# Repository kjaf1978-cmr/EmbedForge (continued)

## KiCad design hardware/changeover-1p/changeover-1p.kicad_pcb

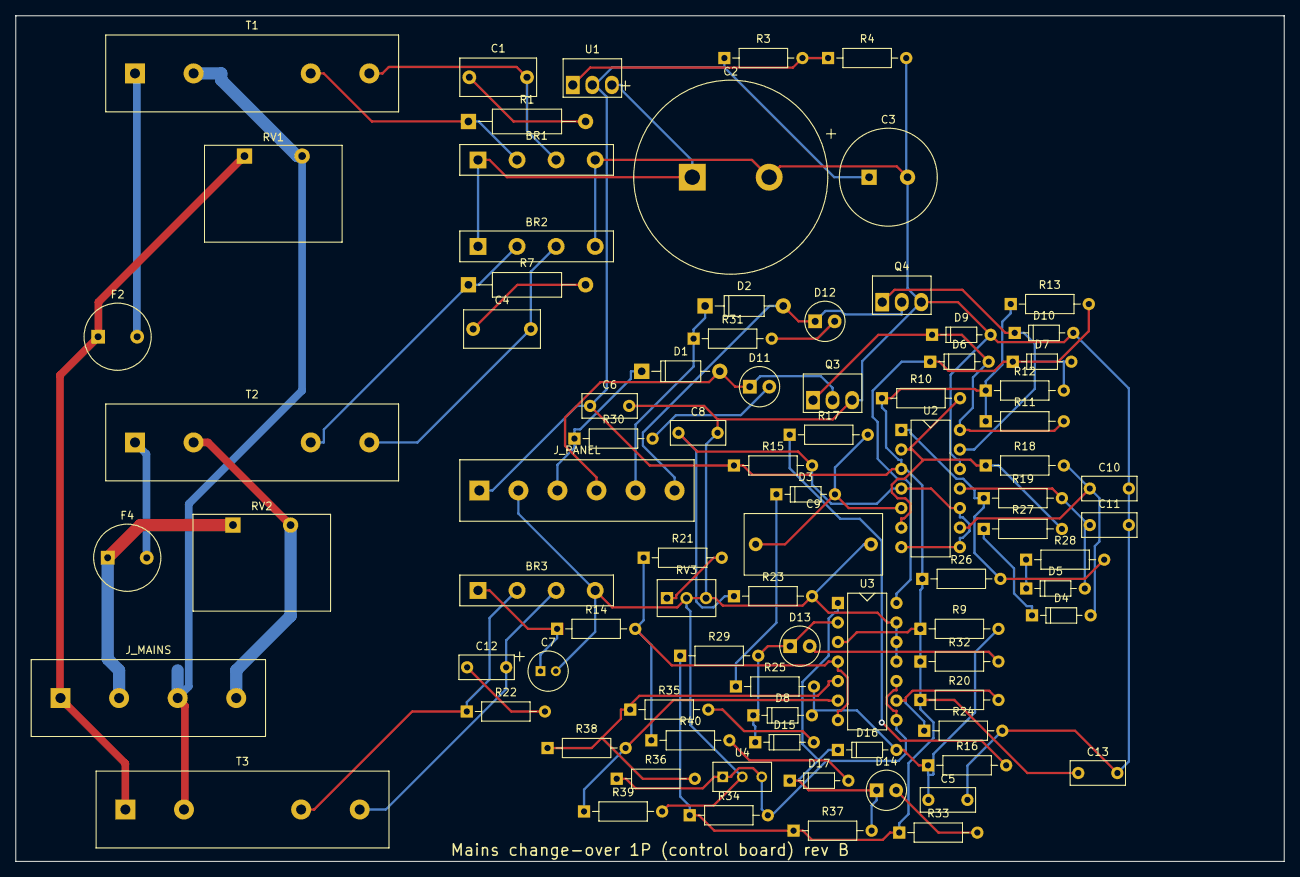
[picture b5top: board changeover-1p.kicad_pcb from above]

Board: 2 copper layers, 165.0 x 110.0 mm, 85 parts (0 on the bottom side), 52 nets.

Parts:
BR1, BR2, BR3: DB107; Bridge_Inline_4
C1, C4: 1u; C_Film_P7.5
C2: 2200u; CP_SnapIn_D25
C3: 100u; CP_Radial_D12.5
C5: 1u; C_Disc_5.08
C6, C8, C12, C13: 100n; C_Disc_5.08
C7: 4.7u; CP_Radial_D5
C9: 10u; C_Film_P15
C10, C11: 680n; C_Disc_5.08
D1, D2: 1N4007; D_DO-41
D3, D4, D5, D6, D7, D8, D15, D16, D17: 1N4148; D_DO-35
D9, D10: BZX55C12; D_DO-35
D11: green; LED_D5.0
D12: yellow; LED_D5.0
D13, D14: red; LED_D5.0
F2, F4: 0.2; F_TR5
J_MAINS: mains to the panel; TerminalBlock_1x4_P7.62
J_PANEL: to the panel; TerminalBlock_1x6
Q3, Q4: IRLZ44N; TO-220_Vertical
R1, R7: 47; R_Axial_0309
R3: 240; R_Axial_0207
R4: 4.42k; R_Axial_0207
R9, R10, R11, R12, R13, R15, R23, R24, R26, R29, R37: 10k; R_Axial_0207
R14, R20: 68k; R_Axial_0207
R16, R17: 750k; R_Axial_0207
R18, R19: 1M; R_Axial_0207
R21: 6.8k; R_Axial_0207
R22: 220; R_Axial_0207
R25, R27, R28, R30, R31, R32, R33: 4.7k; R_Axial_0207
R34: 3.3k; R_Axial_0207
R35: 33k; R_Axial_0207
R36: 2.1k; R_Axial_0207
R38: 4.22k; R_Axial_0207
R39: 12.1k; R_Axial_0207
R40: 100k; R_Axial_0207
RV1, RV2: TMOV14RP300E; TMOV_14
RV3: 5k; Pot_Trimmer_3
T1, T2: 0.13; Transformer_Wires_P7.62
T3: 0.052; Transformer_Wires_P7.62
U1: LM317HV; TO-220_Vertical
U2, U3: LM339; DIP-14
U4: TL431; TO-92_Wide

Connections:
+24V: C3.1, C6.1, C13.1, J_PANEL.1, R3.1, R9.1, R10.1, R11.1, R12.1, R13.1, R15.1, R20.1, R26.1, R29.1, R32.1, R33.1, R34.1, R37.1, U1.2, U2.3, U3.3
A3A: BR1.2, R1.1, T1.3
A3B: BR1.3, C1.2, T1.4
A4A: BR2.2, R7.1, T2.3
A4B: BR2.3, C4.2, T2.4
ADJ: R3.2, R4.1, U1.1
CDT1N: C10.1, D4.2, R18.2, U2.9
CDT2N: C11.1, D5.2, R19.2, U2.11
DTS1: D4.1, R27.1
DTS2: D5.1, R28.1
GND: BR1.4, BR2.4, BR3.4, C2.2, C3.2, C5.2, C6.2, C7.2, C8.2, C9.2, C10.2, C11.2, C13.2, D9.2, D10.2, J_PANEL.2, Q3.3, Q4.3, R4.2, R23.2, R24.2, R39.2, RV3.2, RV3.3, U2.12, U3.11, U3.12, U3.13, U4.2
HOV: D15.2, R35.2
HUV: D17.2, R40.2
K1A: D1.1, J_PANEL.3, R30.1
K1C: D1.2, D11.1, J_PANEL.4, Q3.2
K1EN: D6.2, D9.1, Q3.1, R11.2, U2.14
K2A: D2.1, J_PANEL.5, R31.1
K2C: D2.2, D12.1, J_PANEL.6, Q4.2
K2EN: D7.2, D10.1, Q4.1, R12.2, U2.13
L1B: F2.1, J_MAINS.1, RV1.1, T3.1
L2B: F4.1, J_MAINS.2, RV2.1
LF3: F2.2, T1.1
LF4: F4.2, T2.1
LK1A: D11.2, R30.2
LK2A: D12.2, R31.2
LOVA: D13.2, R32.2
LUVA: D14.2, R33.2
N1: J_MAINS.3, RV1.2, T1.2, T3.2
N2: J_MAINS.4, RV2.2, T2.2
ODS: D3.1, R25.1
OK: C5.1, D8.2, D16.2, R9.2, R16.1, R25.2
OKC: C9.1, D3.2, R17.2, U2.5
OKD: R10.2, R18.1, R27.2, U2.2, U2.6
OKDN: R19.1, R26.2, R28.2, U2.1
ORD: R16.2, R17.1
OVN: D8.1, D13.1, D15.1, R29.2, U3.2
SA: BR3.2, R22.1, T3.3
SB: BR3.3, C12.2, T3.4
SENSE: R14.2, R21.1, R40.1, U3.4, U3.7
SN: C12.1, R22.2
SN3: C1.1, R1.2
SN4: C4.1, R7.2
STR: R21.2, RV3.1
UVL: D6.1, D7.1, R13.2, U3.14
UVN: D14.1, D16.1, D17.1, R37.2, U3.1
V24S: R20.2, R24.1, U3.9
VHI: R35.1, R36.2, R38.1, U3.5
VLO: R38.2, R39.1, U3.6
VRAW: BR1.1, BR2.1, C2.1, U1.3
VREF: R34.2, R36.1, U3.8, U3.10, U4.1, U4.3
VSR: BR3.1, C7.1, R14.1
VTH: C8.1, R15.2, R23.1, U2.4, U2.7, U2.8, U2.10

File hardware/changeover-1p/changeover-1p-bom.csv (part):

"on this board","qty","references","part","value","details","footprint","MPN","maker","distributors (order numbers)","unit EUR","total EUR","price basis"
"yes","3","BR1 BR2 BR3","Bridge rectifier","DB107","","Bridge_Inline_4","DB107","various","any distributor (DIP-4)","0.30","0.90","estimate"
"yes","2","C1 C4","Capacitor","1 µF","voltage rating 100 V","C_Film_P7.5","MKT film 1uF 100 V (e.g. WIMA MKS4, TDK B32529)","WIMA / TDK","any distributor (film)","0.35","0.70","estimate"
"yes","1","C2","Electrolytic capacitor","2.2 mF","voltage rating 63 V","CP_SnapIn_D25","2200uF 63 V 105 °C low-ESR long life (series e.g. Nichicon UHW, Panasonic FC/FR)","Nichicon / Panasonic","Future Electronics / Mouser","3.20","3.20","estimate"
"yes","1","C3","Electrolytic capacitor","100 µF","voltage rating 50 V","CP_Radial_D12.5","100uF 50 V 105 °C (e.g. Panasonic FC series)","Panasonic / Nichicon","any distributor (radial)","0.25","0.25","estimate"
"yes","1","C5","Capacitor","1 µF","voltage rating 50 V","C_Disc_5.08","MKT film 1uF 50 V (e.g. WIMA MKS4, TDK B32529)","WIMA / TDK","any distributor (film)","0.35","0.35","estimate"
"yes","3","C6 C8 C13","Capacitor","100 nF","voltage rating 50 V","C_Disc_5.08","ceramic X7R or MKT 100nF 50 V, 5.08 mm","KEMET / Vishay","any distributor (5.08 mm)","0.12","0.36","estimate"
"yes","1","C7","Electrolytic capacitor","4.7 µF","voltage rating 50 V","CP_Radial_D5","4.7uF 50 V 105 °C (e.g. Panasonic FC series)","Panasonic / Nichicon","any distributor (radial)","0.10","0.10","estimate"
"yes","1","C9","Capacitor","10 µF","voltage rating 50 V","C_Film_P15","MKT film 10uF 50 V (e.g. WIMA MKS4, TDK B32529)","WIMA / TDK","any distributor (film)","0.80","0.80","estimate"
"yes","2","C10 C11","Capacitor","680 nF","voltage rating 50 V","C_Disc_5.08","MKT film 680nF 50 V, 5.08 mm (e.g. WIMA MKS2, TDK B32529)","WIMA / TDK","any distributor (film)","0.25","0.50","estimate"
"yes","1","C12","Capacitor","100 nF","voltage rating 63 V","C_Disc_5.08","ceramic X7R or MKT 100nF 63 V, 5.08 mm","KEMET / Vishay","any distributor (5.08 mm)","0.12","0.12","estimate"
"yes","2","D1 D2","Diode","1N4007","","D_DO-41","1N4007","various","any distributor (DO-41)","0.10","0.20","estimate"
"yes","9","D3 D4 D5 D6 D7 D8 D15 D16 D17","Diode","1N4148","","D_DO-35","1N4148","various","any distributor (DO-35)","0.06","0.54","estimate"
"yes","2","D9 D10","Zener diode","BZX55C12","","D_DO-35","BZX55C12","Vishay","any distributor (DO-35)","0.08","0.16","estimate"
"yes","1","D11","LED","green","","LED_D5.0","5 mm green LED, 20 mA","Kingbright (e.g. L-53GD)","any distributor (5 mm LED)","0.12","0.12","estimate"
"yes","1","D12","LED","yellow","","LED_D5.0","5 mm yellow LED, 20 mA","Kingbright (e.g. L-53YD)","any distributor (5 mm LED)","0.12","0.12","estimate"
"yes","2","D13 D14","LED","red","","LED_D5.0","5 mm red LED, 20 mA","Kingbright (e.g. L-53ID)","any distributor (5 mm LED)","0.12","0.24","estimate"
"yes","2","F2 F4","Fuse","200 mA","cold resistance 2 Ω","F_TR5","FST 5×20 T 0.2 A (Schurter 0034.31xx series) + PCB holder 0031.8201","Schurter","Bürklin (holder) 46G6020","1.20","2.40","estimate"
"yes","2","Q3 Q4","N-channel MOSFET","IRLZ44N","","TO-220_Vertical","IRLZ44NPBF","Infineon","Mouser; LCSC C38774","1.85","3.70","live"
"yes","2","R1 R7","Resistor","47 Ω","power rating 500 mW","R_Axial_0309","metal film 47Ω 0.6 W, 1 %, 50 ppm/K (e.g. Vishay MBB0207)","Vishay / Yageo","any distributor (0207 1 %)","0.08","0.16","estimate"
"yes","1","R3","Resistor","240 Ω","power rating 250 mW","R_Axial_0207","metal film 240Ω 0.6 W, 1 %, 50 ppm/K (e.g. Vishay MBB0207)","Vishay / Yageo","any distributor (0207 1 %)","0.08","0.08","estimate"
"yes","1","R4","Resistor","4.42 kΩ","power rating 250 mW","R_Axial_0207","metal film 4.42kΩ 0.6 W, 1 %, 50 ppm/K (e.g. Vishay MBB0207)","Vishay / Yageo","any distributor (0207 1 %)","0.08","0.08","estimate"
"yes","11","R9 R10 R11 R12 R13 R15 R23 R24 R26 R29 R37","Resistor","10 kΩ","power rating 250 mW","R_Axial_0207","metal film 10kΩ 0.6 W, 1 %, 50 ppm/K (e.g. Vishay MBB0207)","Vishay / Yageo","any distributor (0207 1 %)","0.08","0.88","estimate"
"yes","2","R14 R20","Resistor","68 kΩ","power rating 250 mW","R_Axial_0207","metal film 68kΩ 0.6 W, 1 %, 50 ppm/K (e.g. Vishay MBB0207)","Vishay / Yageo","any distributor (0207 1 %)","0.08","0.16","estimate"
"yes","2","R16 R17","Resistor","750 kΩ","power rating 250 mW","R_Axial_0207","metal film 750kΩ 0.6 W, 1 %, 50 ppm/K (e.g. Vishay MBB0207)","Vishay / Yageo","any distributor (0207 1 %)","0.08","0.16","estimate"
"yes","2","R18 R19","Resistor","1 MΩ","power rating 250 mW","R_Axial_0207","metal film 1MΩ 0.6 W, 1 %, 50 ppm/K (e.g. Vishay MBB0207)","Vishay / Yageo","any distributor (0207 1 %)","0.08","0.16","estimate"
"yes","1","R21","Resistor","6.8 kΩ","power rating 250 mW","R_Axial_0207","metal film 6.8kΩ 0.6 W, 1 %, 50 ppm/K (e.g. Vishay MBB0207)","Vishay / Yageo","any distributor (0207 1 %)","0.08","0.08","estimate"
"yes","1","R22","Resistor","220 Ω","power rating 250 mW","R_Axial_0207","metal film 220Ω 0.6 W, 1 %, 50 ppm/K (e.g. Vishay MBB0207)","Vishay / Yageo","any distributor (0207 1 %)","0.08","0.08","estimate"
"yes","7","R25 R27 R28 R30 R31 R32 R33","Resistor","4.7 kΩ","power rating 250 mW","R_Axial_0207","metal film 4.7kΩ 0.6 W, 1 %, 50 ppm/K (e.g. Vishay MBB0207)","Vishay / Yageo","any distributor (0207 1 %)","0.08","0.56","estimate"
"yes","1","R34","Resistor","3.3 kΩ","power rating 250 mW","R_Axial_0207","metal film 3.3kΩ 0.6 W, 1 %, 50 ppm/K (e.g. Vishay MBB0207)","Vishay / Yageo","any distributor (0207 1 %)","0.08","0.08","estimate"
"yes","1","R35","Resistor","33 kΩ","power rating 250 mW","R_Axial_0207","metal film 33kΩ 0.6 W, 1 %, 50 ppm/K (e.g. Vishay MBB0207)","Vishay / Yageo","any distributor (0207 1 %)","0.08","0.08","estimate"
"yes","1","R36","Resistor","2.1 kΩ","power rating 250 mW","R_Axial_0207","metal film 2.1kΩ 0.6 W, 1 %, 50 ppm/K (e.g. Vishay MBB0207)","Vishay / Yageo","any distributor (0207 1 %)","0.08","0.08","estimate"
"yes","1","R38","Resistor","4.22 kΩ","power rating 250 mW","R_Axial_0207","metal film 4.22kΩ 0.6 W, 1 %, 50 ppm/K (e.g. Vishay MBB0207)","Vishay / Yageo","any distributor (0207 1 %)","0.08","0.08","estimate"
"yes","1","R39","Resistor","12.1 kΩ","power rating 250 mW","R_Axial_0207","metal film 12.1kΩ 0.6 W, 1 %, 50 ppm/K (e.g. Vishay MBB0207)","Vishay / Yageo","any distributor (0207 1 %)","0.08","0.08","estimate"
"yes","1","R40","Resistor","100 kΩ","power rating 250 mW","R_Axial_0207","metal film 100kΩ 0.6 W, 1 %, 50 ppm/K (e.g. Vishay MBB0207)","Vishay / Yageo","any distributor (0207 1 %)","0.08","0.08","estimate"
"yes","2","RV1 RV2","Varistor (MOV)","TMOV14RP300E","","TMOV_14","TMOV14RP300E","Littelfuse","Digi-Key; Mouser","1.60","3.20","estimate"
"yes","1","RV3","Potentiometer","","power rating 500 mW; wiper position 64%","Pot_Trimmer_3","3296W-1-502LF","Bourns","Mouser; Digi-Key","1.90","1.90","estimate"
"yes","2","T1 T2","Transformer","0.13","primary inductance 20 H; coupling 0.995; primary resistance 140 Ω; secondary resistance 1.5 Ω","Transformer_Wires_P7.62","FL 24/24 (or Hahn BV EI 482 series)","Block / Hahn","Bürklin / Reichelt","22.00","44.00","estimate"
"yes","1","T3","Transformer","0.052","primary inductance 100 H; coupling 0.99; primary resistance 2 kΩ; secondary resistance 20 Ω","Transformer_Wires_P7.62","VB 1,0/1/12","Block","RS 074-8411","7.20","7.20","live"
"yes","1","U1","Adjustable regulator","LM317HV","heatsink (case to air) 8 K/W","TO-220_Vertical","LM317HVT/NOPB","Texas Instruments","Mouser 926-LM317HVT/NOPB; RS 197-7244","2.20","2.20","live"
"yes","2","U2 U3","Comparator (4 in one package)","LM339","","DIP-14","LM339N","Texas Instruments","any distributor (DIP-14)","0.45","0.90","estimate"
"yes","1","U4","Shunt reference","TL431","","TO-92_Wide","TL431ACLP","Texas Instruments","any distributor (TO-92)","0.30","0.30","estimate"
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
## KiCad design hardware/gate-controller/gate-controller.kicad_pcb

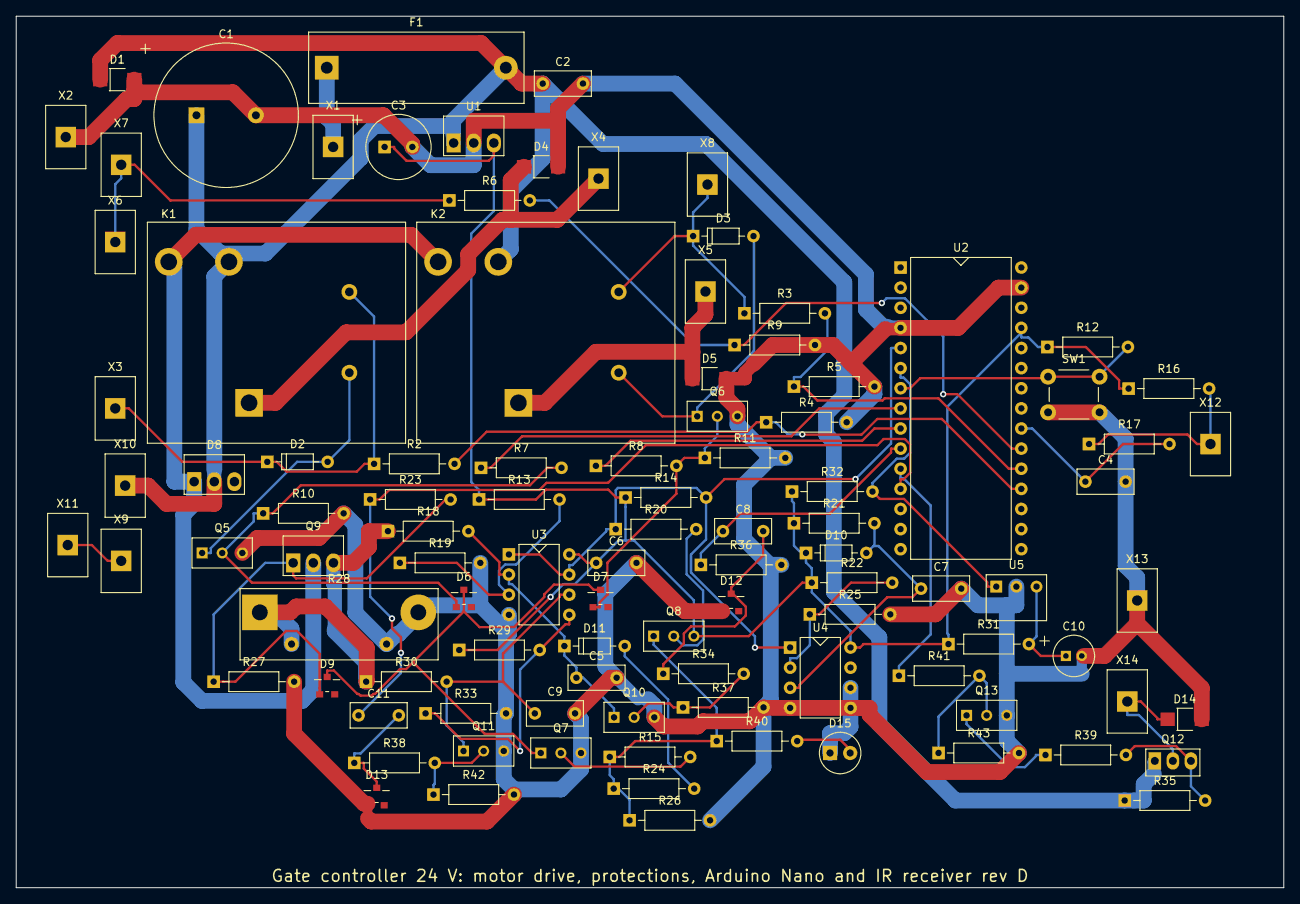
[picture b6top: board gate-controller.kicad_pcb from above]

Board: 2 copper layers, 160.0 x 110.0 mm, 100 parts (0 on the bottom side), 51 nets.

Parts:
C1: 470u; CP_Radial_D18
C2, C4, C6, C7, C8: 100n; C_Disc_5.08
C3: 47u; CP_Radial_D8
C5: 1n; C_Disc_5.08
C9, C11: 1u; C_Disc_5.08
C10: 4.7u; CP_Radial_D5
D1, D4, D5, D14: SMAJ33A; D_SMA
D2, D3, D10, D11: 1N4148; D_DO-35
D6, D7, D9, D12, D13: BAT54; SOT-23
D8: MBR20100CT; TO-220_Vertical
D15: red; LED_D5.0
F1: 10; Fuseholder_5x20
K1, K2: 24 V 30 A; Relay_SPDT_832A
Q5, Q6, Q7, Q10, Q11, Q13: BC547B; TO-92_Wide
Q8: BC557B; TO-92_Wide
Q9: IRLZ44N; TO-220_Vertical
Q12: BD140; TO-126_Vertical
R2, R3, R6, R10, R11, R37, R38, R43: 47k; R_Axial_0207
R4, R5, R7, R8, R9, R12, R14, R16, R20, R22, R24, R26, R27, R32, R34, R35, R41: 10k; R_Axial_0207
R13: 19.1k; R_Axial_0207
R15, R39: 4.7k; R_Axial_0207
R17, R18, R19, R23, R33, R40: 1k; R_Axial_0207
R21: 470k; R_Axial_0207
R25: 39k; R_Axial_0207
R28: 0.01; R_Shunt_4T
R29: 69.8k; R_Axial_0207
R30, R36, R42: 100k; R_Axial_0207
R31: 100; R_Axial_0207
SW1: false; SW_Tactile_6mm
U1: 7805; TO-220_Vertical
U2: Arduino Nano; Arduino_Nano
U3, U4: LM393; DIP-8
U5: TSOP38238; IR_Receiver_TSOP382
X1: +24 V; TerminalBlock_1x1
X2: 0 V; TerminalBlock_1x1
X3: open limit (NC); TerminalBlock_1x1
X4: motor 1; TerminalBlock_1x1
X5: motor 2; TerminalBlock_1x1
X6: close limit (NC), return; TerminalBlock_1x1
X7: photo-beam contact (NC), feed; TerminalBlock_1x1
X8: photo-beam contact (NC), return; TerminalBlock_1x1
X9: limit switches common +24 V; TerminalBlock_1x1
X10: STOP button (NC), feed; TerminalBlock_1x1
X11: STOP button (NC), return; TerminalBlock_1x1
X12: push-button / key-switch (NO); TerminalBlock_1x1
X13: push-button / key-switch, 0 V; TerminalBlock_1x1
X14: photo-beam transmitter +24 V (tested); TerminalBlock_1x1

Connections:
BBL: Q11.2, R38.2, R42.1
BC: D7.1, Q6.2, R8.2, R11.1
BCL: Q10.2, R34.2, R37.1
BFL: Q8.2, R20.2
BFQ: Q7.2, R15.2
BLA: C11.2, D13.3, R38.1
BMC: D3.1, K2.1, R3.1, X8.1
BML: R6.1, X6.1, X7.1
BO: D6.1, Q5.2, R7.2, R10.1
BTB: Q13.2, R41.2, R43.1
BTP: Q12.3, R35.2, R39.2
BTX: R41.1, U2.11
CLOSE: R8.1, U2.9
CLP: C8.2, D12.3, R34.1
CLR: C8.1, R36.1, U2.10
FCL: D6.3, D7.3, D9.3, Q7.1
FLT: Q8.1, R15.1, R24.1, R26.1, R40.1
FLTN: R14.2, R20.1, U2.5, U3.1, U3.7, U4.1
GM: D9.1, Q9.1, R23.2, R27.1
GND: C1.2, C2.2, C3.2, C4.2, C5.2, C6.2, C7.2, C9.2, C10.2, D1.2, D4.2, D5.2, D12.1, D13.1, D14.2, D15.1, Q5.3, Q6.3, Q7.3, Q10.3, Q11.3, Q13.3, R4.2, R5.2, R9.2, R10.2, R11.2, R19.2, R25.2, R26.2, R27.2, R28.2, R28.4, R33.2, R36.2, R37.2, R42.2, R43.2, SW1.2a, SW1.2b, U1.2, U2.4, U2.29, U3.4, U4.4, U4.5, U4.6, U5.2, X2.1, X13.1
IRO: R32.2, U2.6, U5.1
ISF: C9.1, Q11.1, R30.2, U3.6
KCC: D3.2, K2.2, Q6.1
KOC: D2.2, K1.2, Q5.1
KSI: C4.1, R17.2, U2.22
KSW: R16.2, R17.1, X12.1
LBI: R6.2, R9.1, U2.21
LCI: R3.2, R5.1, U2.20
LFA: D15.2, R40.2
LOI: R2.2, R4.1, U2.19
LRN: R12.2, SW1.1a, SW1.1b, U2.7
LSO: D2.1, K1.1, R2.1, X3.1
LTA: D11.2, R24.2
MA: D4.1, K1.3, X4.1
MB: D5.1, K2.3, X5.1
OPEN: R7.1, U2.8
PRC: C7.1, D10.2, R21.2, U4.3
PRD: R22.2, R25.1, U4.2
RUN: C11.1, R23.1, U2.12
SRET: Q9.3, R18.1, R28.1, R28.3, R30.1
SRF: C5.1, D11.1, Q10.1, R18.2, U3.2
SW: D8.1, K1.4, K2.4, Q9.2
TXC: Q13.1, R39.1
V5: C3.1, C6.1, D10.1, Q8.3, R12.1, R13.1, R14.1, R16.1, R21.1, R22.1, R29.1, R31.1, R32.1, U1.3, U2.27, U3.8, U4.8
V24: F1.1, X1.1
V24F: C1.1, C2.1, D1.1, D8.2, F1.2, K1.5, K2.5, Q12.1, R35.1, U1.1, X10.1
VIR: C10.1, R31.2, U5.3
VLIM: X9.1, X11.1
VOB: R29.2, R33.1, U3.5
VSC: R13.2, R19.1, U3.3
VTX: D14.1, Q12.2, X14.1

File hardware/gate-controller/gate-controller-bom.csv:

"on this board","qty","references","part","value","details","footprint","MPN","maker","distributors (order numbers)","unit EUR","total EUR","price basis"
"yes","1","C1","Electrolytic capacitor","470 µF","voltage rating 50 V","CP_Radial_D18","470uF 50 V 105 °C (e.g. Panasonic FC series)","Panasonic / Nichicon","any distributor (radial)","0.25","0.25","estimate"
"yes","5","C2 C4 C6 C7 C8","Capacitor","100 nF","voltage rating 50 V","C_Disc_5.08","ceramic X7R or MKT 100nF 50 V, 5.08 mm","KEMET / Vishay","any distributor (5.08 mm)","0.12","0.60","estimate"
"yes","1","C3","Electrolytic capacitor","47 µF","voltage rating 16 V","CP_Radial_D8","47uF 16 V 105 °C (e.g. Panasonic FC series)","Panasonic / Nichicon","any distributor (radial)","0.10","0.10","estimate"
"yes","1","C5","Capacitor","1 nF","voltage rating 50 V","C_Disc_5.08","C0G ceramic 1nF 50 V, 5.08 mm","KEMET / Vishay","any distributor (5.08 mm)","0.10","0.10","estimate"
"yes","1","C9","Capacitor","1 µF","voltage rating 50 V","C_Disc_5.08","MKT film 1uF 50 V (e.g. WIMA MKS4, TDK B32529)","WIMA / TDK","any distributor (film)","0.35","0.35","estimate"
"yes","1","C10","Electrolytic capacitor","4.7 µF","voltage rating 16 V","CP_Radial_D5","4.7uF 16 V 105 °C (e.g. Panasonic FC series)","Panasonic / Nichicon","any distributor (radial)","0.10","0.10","estimate"
"yes","1","C11","Capacitor","1 µF","voltage rating 16 V","C_Disc_5.08","MKT film 1uF 16 V (e.g. WIMA MKS4, TDK B32529)","WIMA / TDK","any distributor (film)","0.35","0.35","estimate"
"yes","4","D1 D4 D5 D14","TVS diode","SMAJ33A","","D_SMA","SMAJ33A","Littelfuse","LCSC; Mouser","0.20","0.80","estimate"
"yes","4","D2 D3 D10 D11","Diode","1N4148","","D_DO-35","1N4148","various","any distributor (DO-35)","0.06","0.24","estimate"
"yes","5","D6 D7 D9 D12 D13","Diode","BAT54","","SOT-23","BAT54","various","LCSC C47546","0.05","0.25","estimate"
"yes","1","D8","Diode","MBR20100CT","","TO-220_Vertical","MBR20100CTG","onsemi","Mouser; Digi-Key","0.95","0.95","estimate"
"yes","1","D15","LED","red","","LED_D5.0","5 mm red LED, 20 mA","Kingbright (e.g. L-53ID)","any distributor (5 mm LED)","0.12","0.12","estimate"
"yes","1","F1","Fuse","10 A","cold resistance 10 mΩ","Fuseholder_5x20","FST 5×20 T 10 A (Schurter 0034.31xx series) + PCB holder 0031.8201","Schurter","Bürklin (holder) 46G6020","1.20","1.20","estimate"
"yes","2","K1 K2","Relay","24 V 30 A","","Relay_SPDT_832A","832A-1C-S 24VDC","Song Chuan","Mouser (832AWP variant)","3.00","6.00","estimate"
"yes","6","Q5 Q6 Q7 Q10 Q11 Q13","NPN transistor","BC547B","","TO-92_Wide","BC547B","onsemi","any distributor (TO-92)","0.10","0.60","estimate"
"yes","1","Q8","PNP transistor","BC557B","","TO-92_Wide","BC557B","onsemi","any distributor (TO-92)","0.10","0.10","estimate"
"yes","1","Q9","N-channel MOSFET","IRLZ44N","","TO-220_Vertical","IRLZ44NPBF","Infineon","Mouser; LCSC C38774","1.85","1.85","live"
"yes","1","Q12","PNP transistor","BD140","","TO-126_Vertical","BD140-16","STMicroelectronics","any distributor (TO-126)","0.45","0.45","estimate"
"yes","8","R2 R3 R6 R10 R11 R37 R38 R43","Resistor","47 kΩ","power rating 250 mW","R_Axial_0207","metal film 47kΩ 0.6 W, 1 %, 50 ppm/K (e.g. Vishay MBB0207)","Vishay / Yageo","any distributor (0207 1 %)","0.08","0.64","estimate"
"yes","17","R4 R5 R7 R8 R9 R12 R14 R16 R20 R22 R24 R26 R27 R32 R34 R35 R41","Resistor","10 kΩ","power rating 250 mW","R_Axial_0207","metal film 10kΩ 0.6 W, 1 %, 50 ppm/K (e.g. Vishay MBB0207)","Vishay / Yageo","any distributor (0207 1 %)","0.08","1.36","estimate"
"yes","1","R13","Resistor","19.1 kΩ","power rating 250 mW","R_Axial_0207","metal film 19.1kΩ 0.6 W, 1 %, 50 ppm/K (e.g. Vishay MBB0207)","Vishay / Yageo","any distributor (0207 1 %)","0.08","0.08","estimate"
"yes","2","R15 R39","Resistor","4.7 kΩ","power rating 250 mW","R_Axial_0207","metal film 4.7kΩ 0.6 W, 1 %, 50 ppm/K (e.g. Vishay MBB0207)","Vishay / Yageo","any distributor (0207 1 %)","0.08","0.16","estimate"
"yes","6","R17 R18 R19 R23 R33 R40","Resistor","1 kΩ","power rating 250 mW","R_Axial_0207","metal film 1kΩ 0.6 W, 1 %, 50 ppm/K (e.g. Vishay MBB0207)","Vishay / Yageo","any distributor (0207 1 %)","0.08","0.48","estimate"
"yes","1","R21","Resistor","470 kΩ","power rating 250 mW","R_Axial_0207","metal film 470kΩ 0.6 W, 1 %, 50 ppm/K (e.g. Vishay MBB0207)","Vishay / Yageo","any distributor (0207 1 %)","0.08","0.08","estimate"
"yes","1","R25","Resistor","39 kΩ","power rating 250 mW","R_Axial_0207","metal film 39kΩ 0.6 W, 1 %, 50 ppm/K (e.g. Vishay MBB0207)","Vishay / Yageo","any distributor (0207 1 %)","0.08","0.08","estimate"
"yes","1","R28","Resistor","10 mΩ","power rating 3 W","R_Shunt_4T","four-terminal shunt 0.01Ω, 3 W, 1 % (e.g. Isabellenhütte BVR / Vishay WSR: the code for 0.01Ω)","Isabellenhütte / Vishay","any distributor (shunt)","4.00","4.00","estimate"
"yes","1","R29","Resistor","69.8 kΩ","power rating 250 mW","R_Axial_0207","metal film 69.8kΩ 0.6 W, 1 %, 50 ppm/K (e.g. Vishay MBB0207)","Vishay / Yageo","any distributor (0207 1 %)","0.08","0.08","estimate"
"yes","3","R30 R36 R42","Resistor","100 kΩ","power rating 250 mW","R_Axial_0207","metal film 100kΩ 0.6 W, 1 %, 50 ppm/K (e.g. Vishay MBB0207)","Vishay / Yageo","any distributor (0207 1 %)","0.08","0.24","estimate"
"yes","1","R31","Resistor","100 Ω","power rating 250 mW","R_Axial_0207","metal film 100Ω 0.6 W, 1 %, 50 ppm/K (e.g. Vishay MBB0207)","Vishay / Yageo","any distributor (0207 1 %)","0.08","0.08","estimate"
"yes","1","SW1","Push-button","tactile 6 mm","current rating 1 A","SW_Tactile_6mm","tactile switch 6 × 6 mm, THT (e.g. Omron B3F-1000)","Omron","any distributor (tactile)","0.30","0.30","estimate"
"yes","1","U1","Voltage regulator","7805","","TO-220_Vertical","L7805CV","STMicroelectronics","LCSC; Mouser","0.40","0.40","estimate"
"yes","1","U2","Microcontroller module (Arduino Nano, 5 V)","Arduino Nano","","Arduino_Nano","A000005 (Arduino Nano)","Arduino","Mouser 782-A000005; Digi-Key","21.00","21.00","estimate"
"yes","2","U3 U4","Comparator (2 in one package)","LM393","","DIP-8","LM393P","Texas Instruments","any distributor (DIP-8)","0.40","0.80","estimate"
"yes","1","U5","Infrared receiver 38 kHz (TSOP38238)","TSOP38238","","IR_Receiver_TSOP382","TSOP38238","Vishay","Mouser 782-TSOP38238; Digi-Key","1.00","1.00","estimate"
"yes","14","X1 X2 X3 X4 X5 X6 X7 X8 X9 X10 X11 X12 X13 X14","Screw terminal","5.08 mm, 1 pole","functions: X1 +24 V, X2 0 V, X3 open limit (NC), X4 motor 1, X5 motor 2, X6 close limit (NC), return, X7 photo-beam contact (NC), feed, X8 photo-beam contact (NC), return, X9 limit switches common +24 V, X10 STOP button (NC), feed, X11 STOP button (NC), return, X12 push-button / key-switch (NO), X13 push-button / key-switch, 0 V, X14 photo-beam transmitter +24 V (tested)","TerminalBlock_1x1","MKDS 1,5/ 2-5,08 (2 poles per block)","Phoenix Contact","RS 193-0564","0.40","5.60","estimate"

"Parts on this board: EUR 50.79 (unit quantity). Indicative prices, October 2026, EUR without VAT (converted at USD × 0.9, GBP × 1.15): ""live"" from a distributor page or snapshot, ""estimate"" a typical price. Check prices, stock and lead times when ordering; wholesale prices of contactors and breakers are often 40–60 % below distributor list prices."

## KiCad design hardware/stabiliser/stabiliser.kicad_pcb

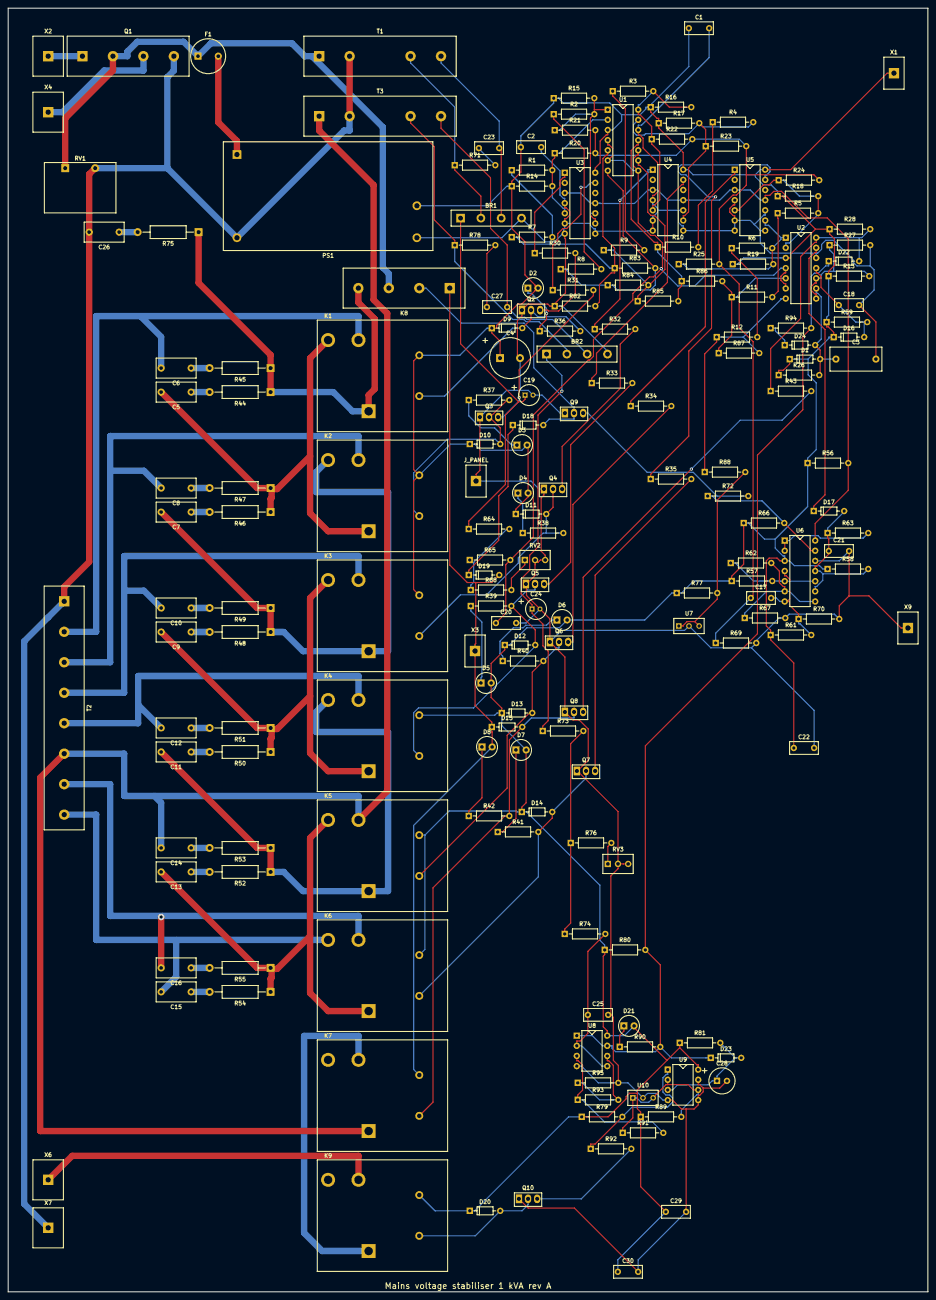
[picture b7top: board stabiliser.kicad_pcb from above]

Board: 2 copper layers, 230.0 x 321.0 mm, 194 parts (0 on the bottom side), 122 nets.

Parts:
BR1, BR2: DB107; Bridge_Inline_4
C1, C2, C17, C22, C23, C27, C29, C30: 100n; C_Disc_5.08
C3: 4.7u; C_Film_P10
C4: 100u; CP_Radial_D10
C5, C6, C7, C8, C9, C10, C11, C12, C13, C14, C15, C16, C26: 100n; C_Film_P7.5
C18, C20, C25: 470n; C_Disc_5.08
C19, C24: 4.7u; CP_Radial_D5
C21: 1u; C_Disc_5.08
C28: 22u; CP_Radial_D6.3
D1, D9, D10, D11, D12, D13, D14, D15, D16, D17, D18, D20, D22, D23, D24: 1N4148; D_DO-35
D2, D3, D4, D5, D6, D7: yellow; LED_D5.0
D8: green; LED_D5.0
D19: BZX85C24; D_DO-35
D21: red; LED_D5.0
F1: 1; F_TR5
J_PANEL: to the panel; TerminalBlock_1x1
K1, K2, K3, K4, K5, K6, K7, K9: 12 V 30 A; Relay_SPDT_832A
K8: 9 A, coil 12 V DC; TerminalBlock_1x4_P7.62
PS1: IRM-15-12; IRM-15
Q1: 10; TerminalBlock_1x4_P7.62
Q2, Q3, Q4, Q5, Q6, Q7, Q8, Q9, Q10: BD139; TO-126_Vertical
R1, R2, R3, R4, R5, R6, R7, R8, R9, R10, R11, R12, R26, R59: 1M; R_Axial_0207
R13: 2.49k; R_Axial_0207
R14, R15, R16, R17, R18, R19, R28, R36, R37, R38, R39, R40, R41, R42, R43, R66, R72, R77, R79, R89, R92, R94: 2.2k; R_Axial_0207
R20, R21, R22, R23, R24, R25, R57, R61, R65, R67, R69, R70, R74: 100k; R_Axial_0207
R27, R56, R62, R80, R95: 10k; R_Axial_0207
R30, R31, R32, R33, R34, R35, R90: 4.7k; R_Axial_0207
R44, R45, R46, R47, R48, R49, R50, R51, R52, R53, R54, R55, R75: 100; R_Axial_0309
R58: 61.9k; R_Axial_0207
R63: 1k; R_Axial_0207
R64: 80.6k; R_Axial_0207
R68: 6.8k; R_Axial_0207
R71, R78: 220; R_Axial_0207
R73: 806k; R_Axial_0207
R76: 68k; R_Axial_0207
R81: 47k; R_Axial_0207
R82: 5.36k; R_Axial_0207
R83, R84, R85, R86: 732; R_Axial_0207
R87: 909; R_Axial_0207
R88: 787; R_Axial_0207
R91: 1.82k; R_Axial_0207
R93: 3.65k; R_Axial_0207
RV1: TMOV14RP300E; TMOV_14
RV2: 5k; Pot_Trimmer_3
RV3: 50k; Pot_Trimmer_3
T1, T3: 0.06; Transformer_Wires_P7.62
T2: 1 kVA 230 V, taps 150-280 V; TerminalBlock_1x8_P7.62
U1, U2, U6: LM339; DIP-14
U3, U4, U5: +12V; DIP-14
U7, U10: TL431; TO-92_Wide
U8, U9: LM393; DIP-8
X1: thermal cut-out of T (NC); TerminalBlock_1x1
X2: L in; TerminalBlock_1x1_P7.62
X3: thermal cut-out of T, return; TerminalBlock_1x1
X4: N in; TerminalBlock_1x1_P7.62
X6: L out; TerminalBlock_1x1_P7.62
X7: N out; TerminalBlock_1x1_P7.62
X9: PE stud (control ground); TerminalBlock_1x1

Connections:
+12V: C1.1, C2.1, C4.1, C22.1, C29.1, C30.1, D1.1, D2.2, D3.2, D4.2, D5.2, D6.2, D7.2, D9.1, D10.1, D11.1, D12.1, D13.1, D14.1, D16.1, D20.1, D21.2, K1.1, K2.1, K3.1, K4.1, K5.1, K6.1, K9.1, PS1.+V, R13.1, R14.1, R15.1, R16.1, R17.1, R18.1, R19.1, R26.1, R28.1, R56.1, R57.1, R58.1, R59.1, R61.1, R66.1, R77.1, R79.1, R80.1, R81.1, R89.1, U1.3, U2.3, U3.14, U4.14, U5.14, U6.3, U8.8, U9.8, X1.1
B1: Q2.3, R30.2
B2: Q3.3, R31.2
B3: Q4.3, R32.2
B4: Q5.3, R33.2
B5: Q6.3, R34.2
B6: Q7.3, R35.2
BD: Q8.3, R43.2
BI: Q9.3, R72.2
BP: Q10.3, R92.2
BPP: C28.1, D23.2, R81.2, U9.3
C2N: C5.2, K1.4, K2.3, R46.1, R47.1
C3N: C7.2, K2.4, K3.3, R48.1, R49.1
C4N: C9.2, K3.4, K4.3, R50.1, R51.1
C5N: C11.2, K4.4, K5.3, R52.1, R53.1
C6N: C13.2, K5.4, K6.3, R54.1, R55.1
CLK: R56.2, U3.3, U3.11, U4.3, U4.11, U5.3, U5.11, U6.14
DF2K: D24.1, R94.1
DIZ: D18.1, D19.1
DLY: C3.1, D1.2, D24.2, R26.2, U2.9
DTH: R13.2, R27.1, U2.8, U2.10
E: C17.2, R61.2, R70.1, U6.4, U6.7
FLTS: D22.1, D23.1, R80.2, R90.2, R94.2, U8.1, U8.7
GND: BR1.4, BR2.4, C1.2, C2.2, C3.2, C4.2, C18.2, C19.2, C20.2, C21.2, C22.2, C24.2, C25.2, C28.2, C29.2, C30.2, J_PANEL.1, PS1.-V, Q2.1, Q3.1, Q4.1, Q5.1, Q6.1, Q7.1, Q8.1, Q9.1, Q10.1, R27.2, R67.2, R69.2, R70.2, R82.1, R95.2, RV2.2, RV2.3, RV3.2, RV3.3, U1.12, U2.12, U3.4, U3.6, U3.7, U3.8, U3.10, U4.4, U4.6, U4.7, U4.8, U4.10, U5.4, U5.6, U5.7, U5.8, U5.10, U6.12, U7.2, U8.4, U9.4, U9.5, U9.7, U10.2, X9.1
K1: D9.2, K1.2, Q2.2, R36.2
K2: D10.2, K2.2, Q3.2, R37.2
K3: D11.2, K3.2, Q4.2, R38.2
K4: D12.2, K4.2, Q5.2, R39.2
K5: D13.2, K5.2, Q6.2, R40.2
K6: D14.2, K6.2, Q7.2, R41.2
KD: D15.2, K7.2, Q8.2, R42.2
KIC: D18.2, K8.2, Q9.2
KPC: D20.2, K9.2, Q10.2
LFA: D21.1, R90.1
LKA1: D2.1, R36.1
LKA2: D3.1, R37.1
LKA3: D4.1, R38.1
LKA4: D5.1, R39.1
LKA5: D6.1, R40.1
LKA6: D7.1, R41.1
LKOA: D8.1, R42.1
L_IN: Q1.1, X2.1
MT: C21.1, D17.2, R58.2, R63.1, U6.9, U6.11
N: C26.2, PS1.N, Q1.4, RV1.2, T1.2, T2.1, T3.2, X7.1
N1: R7.1, R82.2, R83.1, U1.5
N2: R8.1, R83.2, R84.1, U1.7
N3: R9.1, R84.2, R85.1, U1.9
N4: R10.1, R85.2, R86.1, U1.11
N5: R11.1, R86.2, R87.1, U2.5
N6: R12.1, R87.2, R88.1, U2.7
NF1: R1.1, R7.2
NF2: R2.1, R8.2
NF3: R3.1, R9.2
NF4: R4.1, R10.2
NF5: R5.1, R11.2
NF6: R6.1, R12.2
N_IN: Q1.3, X4.1
O1: R1.2, R14.2, R20.1, U1.2, U3.5
O2: R2.2, R15.2, R21.1, U1.1, U3.9
O3: R3.2, R16.2, R22.1, U1.14, U4.5
O4: R4.2, R17.2, R23.1, U1.13, U4.9
O5: R5.2, R18.2, R24.1, U2.2, U5.5
O6: R6.2, R19.2, R25.1, U2.1, U5.9
OD: D22.2, R28.2, R43.1, U2.14
OI: R66.2, R72.1, U6.13
OKP: R79.2, R92.1, U9.1
OUT: K9.5, X6.1
OUTK: K7.5, K9.3
PGC: C18.1, D16.2, R59.2, U2.11
PGN: D17.1, U2.13
QF1: R30.1, U3.1
QF2: R31.1, U3.13
QF3: R32.1, U4.1
QF4: R33.1, U4.13
QF5: R34.1, U5.1
QF6: R35.1, U5.13
SA: BR1.2, R71.1, T1.3
SA2: BR2.2, R78.1, T3.3
SB: BR1.3, C23.2, T1.4
SB2: BR2.3, C27.2, T3.4
SEN2: R73.2, R74.1, R76.1
SENSE: R64.2, R65.1, R68.1
SF: C20.1, R65.2, U1.4, U1.6, U1.8, U1.10, U2.4, U2.6
SF2: C25.1, R74.2, U8.2, U8.5
SN: C23.1, R71.2
SN2: C27.1, R78.2
SNA1: C6.1, R45.2
SNA2: C8.1, R47.2
SNA3: C10.1, R49.2
SNA4: C12.1, R51.2
SNA5: C14.1, R53.2
SNA6: C16.1, R55.2
SNC1: C5.1, R44.2
SNC2: C7.1, R46.2
SNC3: C9.1, R48.2
SNC4: C11.1, R50.2
SNC5: C13.1, R52.2
SNC6: C15.1, R54.2
SNKI: C26.1, R75.2
STR: R68.2, RV2.1
STR2: R76.2, RV3.1
SUM: C17.1, R20.2, R21.2, R22.2, R23.2, R24.2, R25.2, R69.1
T1: C6.2, K1.5, T2.2
T2: C8.2, K2.5, T2.3
T3: C10.2, K3.5, T2.4
T4: C12.2, K4.5, T2.5
T5: C14.2, K5.5, K7.3, T2.6, T3.1
T6: C16.2, K6.5, T2.7
T7: C15.2, K6.4, T2.8
TRG: R63.2, U6.1, U6.2
VCH: K1.3, K8.4, R44.1, R45.1, R75.1
VEH: R57.2, R62.1, U6.5, U6.10
VEL: R62.2, R67.1, U6.6, U6.8
VF: F1.2, PS1.L
VIN: F1.1, K8.3, Q1.2, RV1.1, T1.1
VOV: R91.2, R93.1, U8.3
VREF: R77.2, R88.2, U7.1, U7.3
VREF2: R89.2, R91.1, U9.2, U9.6, U10.1, U10.3
VSR: BR1.1, C19.1, R64.1
VSR2: BR2.1, C24.1, R73.1
VTC: D8.2, D15.1, D19.2, K7.1, K8.1, X3.1
VUV: R93.2, R95.1, U8.6

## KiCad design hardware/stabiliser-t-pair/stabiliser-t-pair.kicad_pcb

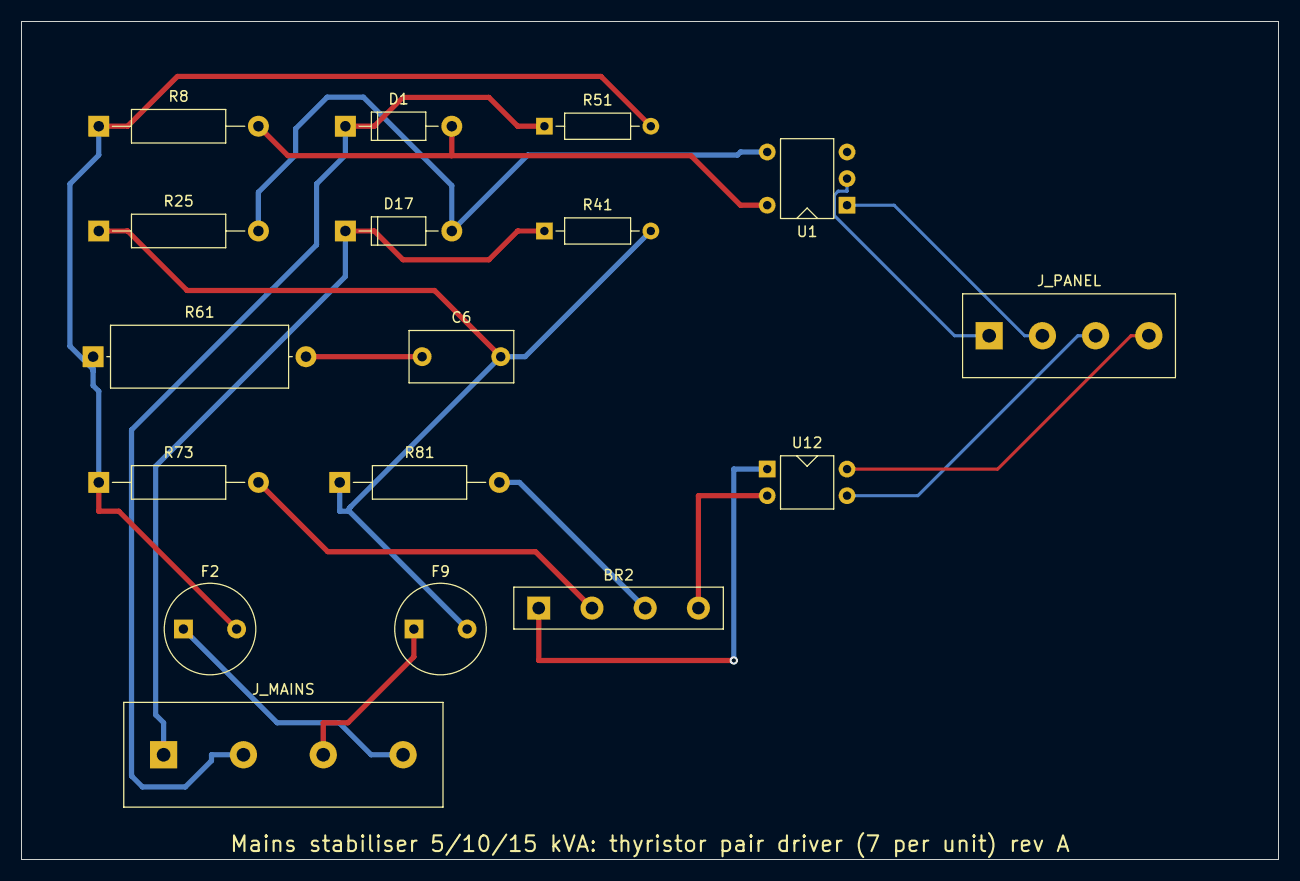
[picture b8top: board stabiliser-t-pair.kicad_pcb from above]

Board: 2 copper layers, 120.0 x 80.0 mm, 17 parts (0 on the bottom side), 17 nets.

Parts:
BR2: DB107; Bridge_Inline_4
C6: 100n; C_Film_P7.5
D1, D17: 1N4007; D_DO-41
F2, F9: 0.5; F_TR5
J_MAINS: mains to the panel; TerminalBlock_1x4_P7.62
J_PANEL: to the panel; TerminalBlock_1x4
R8, R25: 470; R_Axial_0309
R41, R51: 1k; R_Axial_0207
R61: 47; R_Axial_P20
R73, R81: 22k; R_Axial_0309
U1: FOD4218; DIP-6_NoPin5
U12: PC817; DIP-4

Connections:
GA1: D17.1, J_MAINS.1, R41.1
GB1: D1.1, J_MAINS.2, R51.1
LK1: J_PANEL.1, U1.2
LO1A: J_PANEL.2, U1.1
OC1: J_PANEL.3, U12.3
OFFN: J_PANEL.4, U12.4
SNB1: C6.1, R61.2
SW1: F2.2, R8.1, R51.2, R61.1, R73.1
T1: F9.1, J_MAINS.3
TK1: C6.2, F9.2, R25.1, R41.2, R81.1
VSA1: BR2.2, R73.2
VSB1: BR2.3, R81.2
VSN1: BR2.4, U12.2
VSP1: BR2.1, U12.1
VSW: F2.1, J_MAINS.4
XA1: D1.2, R8.2, U1.6
YB1: D17.2, R25.2, U1.4
